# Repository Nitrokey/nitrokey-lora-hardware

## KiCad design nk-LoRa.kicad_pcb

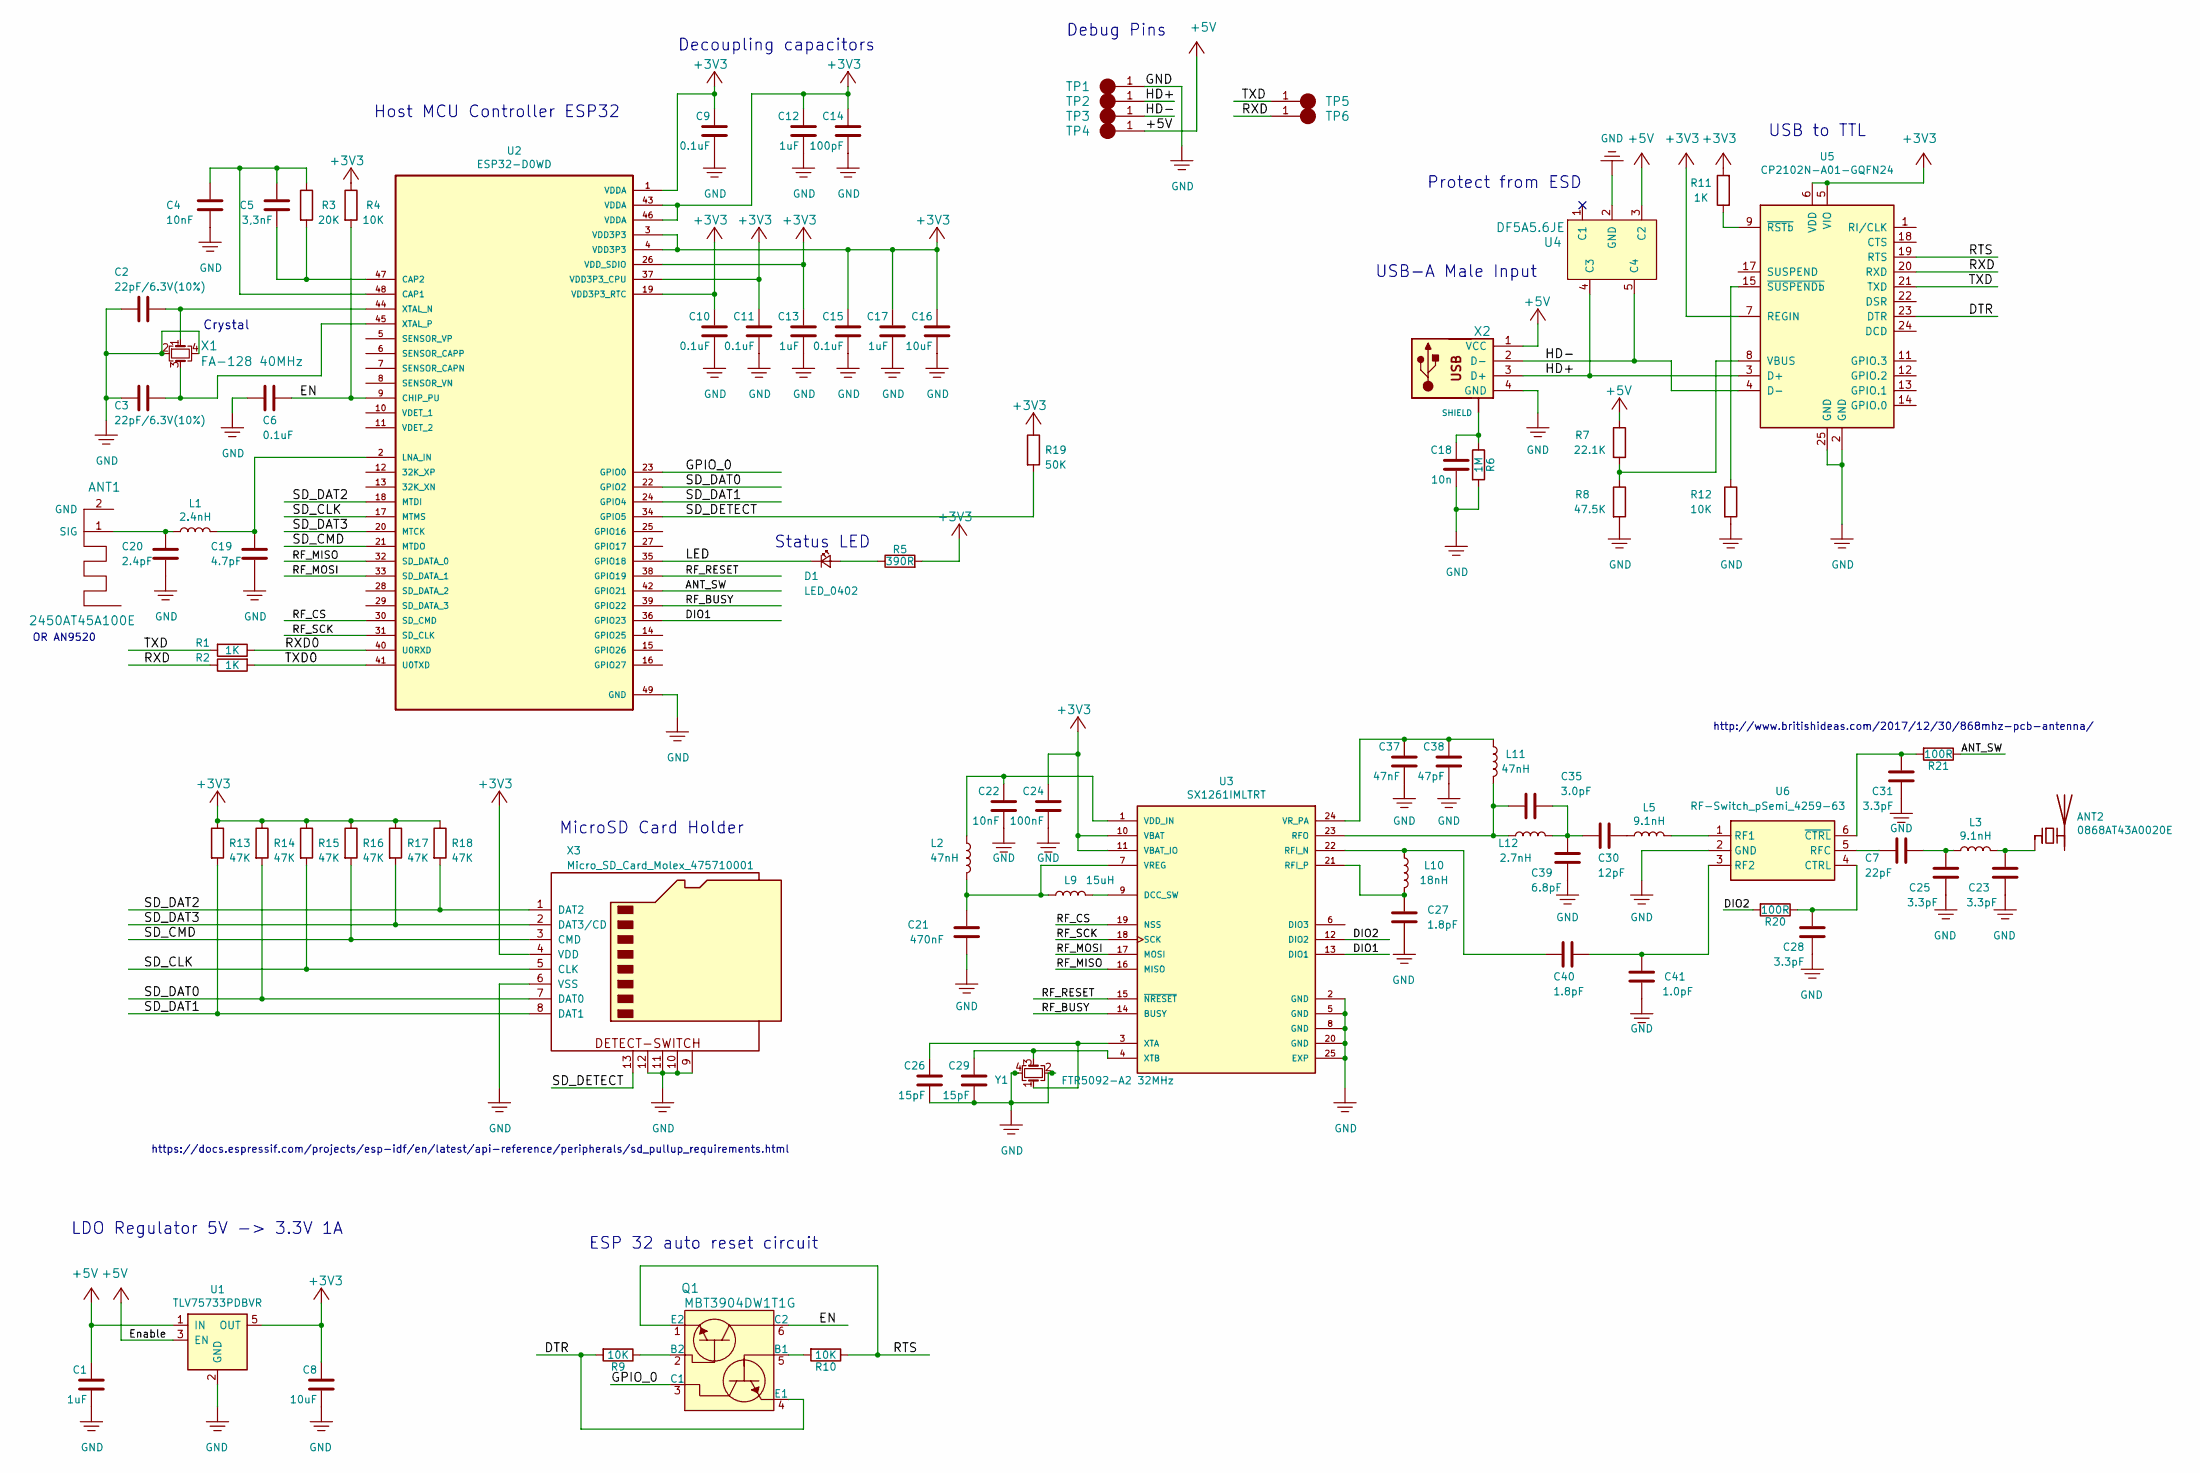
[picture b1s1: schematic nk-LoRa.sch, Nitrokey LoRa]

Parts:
ANT1: 2450AT45A100E; 9520_WiFiChipAntenna
ANT2: 0868AT43A0020E; Ant_868MHz_0868AT43A0020E
C1, C12, C13, C17: 1uF; C_0402_1005Metric; MFG Part Num ?
C2, C3: 22pF/6.3V(10%); C_0402_1005Metric; MFG Part Num ?
C4, C22: 10nF; C_0402_1005Metric; MFG Part Num ?
C5: 3,3nF; C_0402_1005Metric; MFG Part Num ?
C6, C9, C10, C11, C15: 0.1uF; C_0402_1005Metric; MFG Part Num ?
C7: 22pF; C_0402_1005Metric
C8, C16: 10uF; C_0603_1608Metric; MFG Part Num ?
C14: 100pF; C_0402_1005Metric; MFG Part Num ?
C18: 10n; C_0402_1005Metric; MFG Part Num ?
C19: 4.7pF; C_0402_1005Metric
C20: 2.4pF; C_0402_1005Metric
C21: 470nF; C_0402_1005Metric; MFG Part Num GRM155R61A474KE15D
C23, C25, C28, C31: 3.3pF; C_0402_1005Metric
C24: 100nF; C_0402_1005Metric; MFG Part Num GRM155R71C104KA88D
C26, C29: 15pF; C_0402_1005Metric; MFG Part Num GRM1555C1H150JA01D
C27, C40: 1.8pF; C_0402_1005Metric; MFG Part Num GRM1555C1H1R8BA01D
C30: 12pF; C_0402_1005Metric
C35: 3.0pF; C_0402_1005Metric; MFG Part Num GRM1555C1H3R0BA01D
C37: 47nF; C_0402_1005Metric; MFG Part Num ?
C38: 47pF; C_0402_1005Metric; MFG Part Num ?
C39: 6.8pF; C_0402_1005Metric; MFG Part Num GRM1555C1H6R8BA01D
C41: 1.0pF; C_0402_1005Metric
D1: LED_0402; LED_0402_1005Metric
L1: 2.4nH; L_0402_1005Metric; Part.Nr LQP15MN2N4B02D
L2, L11: 47nH; L_0402_1005Metric; Part.Nr LQW15AN47NJ00D
L3, L5: 9.1nH; L_0402_1005Metric; Part.Nr LQW15AN9N1H00D
L9: 15uH; L_0805_2012Metric; Part.Nr MLZ2012M150W
L10: 18nH; L_0402_1005Metric; Part.Nr LQW15AN18NH00D
L12: 2.7nH; L_0402_1005Metric; Part.Nr LQW15AN2N7C00D
Q1: MBT3904DW1T1G; SOT-363_SC-70-6; MPN MBT3904DW1T1G; Digi-Key_PN MBT3904DW1T1GOSCT-ND
R1, R2, R11: 1K; R_0402_1005Metric; MFG Part Num ?
R3: 20K; R_0402_1005Metric; MFG Part Num ?
R4, R9, R10, R12: 10K; R_0402_1005Metric; MFG Part Num ?
R5: 390R; R_0402_1005Metric; MFG Part Num ?
R6: 1M; R_0402_1005Metric; MFG Part Num ?
R7: 22.1K; R_0402_1005Metric; MFG Part Num ?
R8: 47.5K; R_0402_1005Metric; MFG Part Num ?
R13, R14, R15, R16, R17, R18: 47K; R_0402_1005Metric; MFG Part Num ?
R19: 50K; R_0402_1005Metric; MFG Part Num ?
R20, R21: 100R; R_0402_1005Metric; MFG Part Num ?
TP1, TP2, TP3, TP4, TP5, TP6: debug-pin; Prog_Pad_Circular
U1: TLV75733PDBVR; SOT-23-5
U2: ESP32-D0WD; QFN-48-1EP_5x5mm_P0.35mm_EP3.7x3.7mm_ThermalVias
U3: SX1261IMLTRT; QFN-24-1EP_4x4mm_P0.5mm_EP2.7x2.7mm_ThermalVias
U4: DF5A5.6JE; SOT-553; MFG Part Num DF5A5.6JE,LM
U5: CP2102N-A01-GQFN24; QFN-24-1EP_4x4mm_P0.5mm_EP2.6x2.6mm
U6: RF-Switch_pSemi_4259-63; SC-70-6
X1: FA-128 40MHz; Crystal_SMD_2016-4Pin_2.0x1.6mm
X2: USB_Plug; USB-A-PLUG
X3: Micro_SD_Card_Molex_475710001; 47571-0001
Y1: FTR5092-A2 32MHz; Crystal_SMD_2016-4Pin_2.0x1.6mm

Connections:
+3V3: C8.1, C9.1, C10.1, C11.1, C12.1, C13.1, C14.1, C15.1, C16.1, C17.1, C24.1, R4.1, R5.2, R11.2, R13.1, R14.1, R15.1, R16.1, R17.1, R18.1, R19.1, U1.5 (OUT), U2.1 (VDDA), U2.3 (VDD3P3), U2.4 (VDD3P3), U2.19 (VDD3P3_RTC), U2.26 (VDD_SDIO), U2.37 (VDD3P3_CPU), U2.43 (VDDA), U2.46 (VDDA), U3.10 (VBAT), U3.11 (VBAT_IO), U5.5 (VIO), U5.6 (VDD), U5.7 (REGIN), X3.4 (VDD)
+5V: C1.1, R7.1, TP4.1, U1.1 (IN), U1.3 (EN), U4.3 (C2), X2.1 (VCC)
/ANT_SW: R21.1, U2.42 (GPIO21)
/DIO1: U2.36 (GPIO23), U3.13 (DIO1)
/DIO2: R20.2, U3.12 (DIO2)
/DTR: Q1.4 (E1), R9.2, U5.23 (DTR)
/EN: C6.1, Q1.6 (C2), R4.2, U2.9 (CHIP_PU)
/GPIO_0: Q1.3 (C1), U2.23 (GPIO0)
/HD+: TP2.1, U4.4 (C3), U5.3 (D+), X2.3 (D+)
/HD-: TP3.1, U4.5 (C4), U5.4 (D-), X2.2 (D-)
/LED: D1.1 (K), U2.35 (GPIO18)
/RF_BUSY: U2.39 (GPIO22), U3.14 (BUSY)
/RF_CS: U2.30 (SD_CMD), U3.19 (NSS)
/RF_MISO: U2.32 (SD_DATA_0), U3.16 (MISO)
/RF_MOSI: U2.33 (SD_DATA_1), U3.17 (MOSI)
/RF_RESET: U2.38 (GPIO19), U3.15 (~NRESET~)
/RF_SCK: U2.31 (SD_CLK), U3.18 (SCK)
/RTS: Q1.1 (E2), R10.1, U5.19 (RTS)
/RXD: R2.1, TP6.1, U5.20 (RXD)
/RXD0: R1.1, U2.40 (U0RXD)
/SD_CLK: R15.2, U2.17 (MTMS), X3.5 (CLK)
/SD_CMD: R16.2, U2.21 (MTDO), X3.3 (CMD)
/SD_DAT0: R14.2, U2.22 (GPIO2), X3.7 (DAT0)
/SD_DAT1: R13.2, U2.24 (GPIO4), X3.8 (DAT1)
/SD_DAT2: R18.2, U2.18 (MTDI), X3.1 (DAT2)
/SD_DAT3: R17.2, U2.20 (MTCK), X3.2 (DAT3/CD)
/SD_DETECT: R19.2, U2.34 (GPIO5), X3.13 (GND)
/TXD: R1.2, TP5.1, U5.21 (TXD)
/TXD0: R2.2, U2.41 (U0TXD)
GND: C1.2, C2.2, C3.2, C4.1, C6.2, C8.2, C9.2, C10.2, C11.2, C12.2, C13.2, C14.2, C15.2, C16.2, C17.2, C18.2, C19.2, C20.2, C21.2, C22.2, C23.2, C24.2, C25.2, C26.2, C27.1, C28.2, C29.2, C31.2, C37.2, C38.2, C39.1, C41.2, R6.2, R8.2, R12.2, TP1.1, U1.2 (GND), U2.49 (GND), U3.2 (GND), U3.5 (GND), U3.8 (GND), U3.20 (GND), U3.25 (EXP), U4.2 (GND), U5.2 (GND), U5.25 (GND), U6.2 (GND), X1.2, X1.4, X2.4 (GND), X3.6 (VSS), X3.9 (SW1), X3.10 (SW2), X3.11 (GND), X3.12 (GND), Y1.2, Y1.4
unnamed: ANT1.1 (SIG), C20.1, L1.1
unnamed: ANT2.1 (FEED), C23.1, L3.1
unnamed: C2.1, U2.44 (XTAL_N), X1.1
unnamed: C3.1, U2.45 (XTAL_P), X1.3
unnamed: C4.2, C5.1, R3.1, U2.48 (CAP1)
unnamed: C5.2, R3.2, U2.47 (CAP2)
unnamed: C7.2, U6.5 (RFC)
unnamed: C18.1, R6.1, X2.5 (NC1), X2.6 (SHIELD)
unnamed: C19.1, L1.2, U2.2 (LNA_IN)
unnamed: C21.1, L2.1, L9.2, U3.7 (VREG)
unnamed: C22.1, L2.2, U3.1 (VDD_IN)
unnamed: C7.1, C25.1, L3.2
unnamed: C26.1, U3.3 (XTA), Y1.1
unnamed: C27.2, L10.2, U3.21 (RFI_P)
unnamed: C28.1, R20.1, U6.4 (CTRL)
unnamed: C29.1, U3.4 (XTB), Y1.3
unnamed: C30.1, L5.2
unnamed: C30.2, C35.1, C39.2, L12.2
unnamed: C31.1, R21.2, U6.6 (~CTRL)
unnamed: C35.2, L11.1, L12.1, U3.23 (RFO)
unnamed: C37.1, C38.1, L11.2, U3.24 (VR_PA)
unnamed: C40.1, C41.1, U6.3 (RF2)
unnamed: C40.2, L10.1, U3.22 (RFI_N)
unnamed: D1.2 (A), R5.1
unnamed: L5.1, U6.1 (RF1)
unnamed: L9.1, U3.9 (DCC_SW)
unnamed: Q1.2 (B2), R9.1
unnamed: Q1.5 (B1), R10.2
unnamed: R7.2, R8.1, U5.8 (VBUS)
unnamed: R11.1, U5.9 (~RSTb)
unnamed: R12.1, U5.15 (~SUSPENDb)

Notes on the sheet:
Protect from ESD
USB-A Male Input
Host MCU Controller ESP32
Status LED
Decoupling capacitors
Debug Pins
ESP 32 auto reset circuit
USB to TTL
MicroSD Card Holder
Crystal
http://www.britishideas.com/2017/12/30/868mhz-pcb-antenna/
https://docs.espressif.com/projects/esp-idf/en/latest/api-reference/peripherals/sd_pullup_requirements.html
OR AN9520
LDO Regulator 5V -> 3.3V 1A

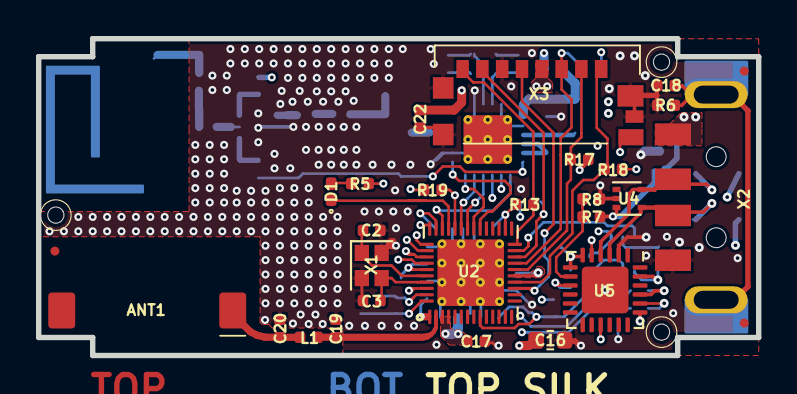
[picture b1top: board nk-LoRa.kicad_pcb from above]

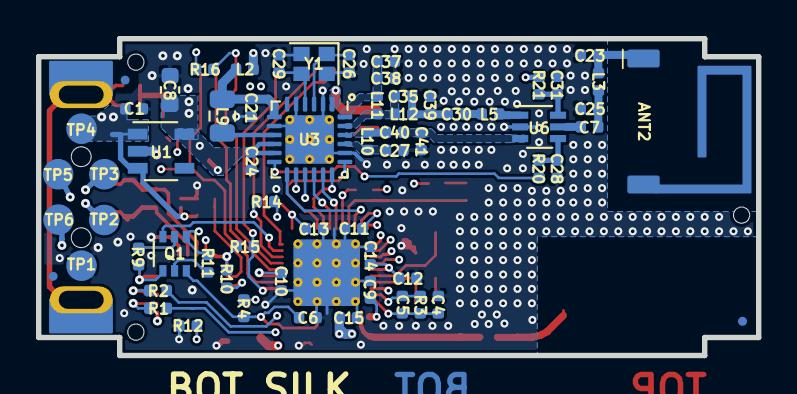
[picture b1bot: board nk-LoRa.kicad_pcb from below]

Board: 4 copper layers, 40.0 x 17.6 mm, 93 parts (65 on the bottom side), 61 nets.

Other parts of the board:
3D_*: case_bottom
FID3, FID3#2, FID3#3, FID3#4, FID3#5, FID3#6: Fiducial_0.5mm_Dia_1mm_Outer

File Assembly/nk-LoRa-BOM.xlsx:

BOM - NITROKEY LoRa Rev.1
Reference | Quantity | Value | Footprint | Manufacturer Part Number | Distributer Link
ANT1 | 1 | 2450 MHZ ANTENNA | footprints:9520_WiFiChipAntenna | 2450AT45A100E | https://www.mouser.de/ProductDetail/Johanson-Technology/2450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
ANT2 | 1 | 868 MHZ ANTENNA | footprints:Ant_868MHz_0868AT43A0020E | 0868AT43A0020E | https://www.digikey.com/product-detail/en/johanson-technolog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
C14 | 1 | 100pF | Capacitor_SMD:C_0402_1005Metric | GRM1555C1H101FA01J | https://www.mouser.de/ProductDetail/Murata-Electronics/GRM15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
C16 C8 | 2 | 10uF | Capacitor_SMD:C_0603_1608Metric | GRM188R61A106KE69J | https://www.mouser.de/ProductDetail/Murata-Electronics/GRM18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
C1 C12 C13 C17 | 4 | 1uF | Capacitor_SMD:C_0402_1005Metric | GRM155C81A105KA12D | https://www.mouser.de/ProductDetail/Murata-Electronics/GRM15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
C18 | 1 | 10n | Capacitor_SMD:C_0402_1005Metric | GRM155R71E103KA01D | https://www.mouser.de/ProductDetail/Murata-Electronics/GRM15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
C19 | 1 | 4.7pF | Capacitor_SMD:C_0402_1005Metric | GJM1555C1H2R4CB01D | https://www.mouser.de/ProductDetail/Murata-Electronics/GJM15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
C2 C3 | 2 | 22pF/6.3V(10%) | Capacitor_SMD:C_0402_1005Metric | GRM1555C1H220FA01D | https://www.mouser.de/ProductDetail/Murata-Electronics/GRM15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
C20 | 1 | 2.4pF | Capacitor_SMD:C_0402_1005Metric | GJM1555C1H2R4CB01J | https://www.mouser.de/ProductDetail/Murata-Electronics/GJM15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
C21 | 1 | 470nF | Capacitor_SMD:C_0402_1005Metric | GRM155R61A474KE15D | https://www.mouser.de/ProductDetail/Murata-Electronics/GRM15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
C23 C25 C28 C31 | 4 | 3.3pF | Capacitor_SMD:C_0402_1005Metric | GRM1555C1H3R3BA01D | https://www.mouser.de/ProductDetail/Murata-Electronics/GRM15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
C27 C40 | 2 | 1.8pF | Capacitor_SMD:C_0402_1005Metric | GRM1555C1H1R8BA01D | https://www.mouser.de/_/?Keyword=GRM1555C1H1R8BA01D
C26 C29 | 2 | 15pF | Capacitor_SMD:C_0402_1005Metric | GRM1555C1H150JA01D | https://www.mouser.de/ProductDetail/Murata-Electronics/GRM15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
C30 | 1 | 12pF | Capacitor_SMD:C_0402_1005Metric | GRM1555C1H120JA01J | https://www.mouser.de/ProductDetail/Murata-Electronics/GRM15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
C35 | 1 | 3.0pF | Capacitor_SMD:C_0402_1005Metric | GRM1555C1H3R0BA01D | https://www.mouser.de/ProductDetail/Murata-Electronics/GRM15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
C37 | 1 | 47nF | Capacitor_SMD:C_0402_1005Metric | GRM155R71C473KA01J | https://www.mouser.de/ProductDetail/Murata-Electronics/GRM15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
C38 | 1 | 47pF | Capacitor_SMD:C_0402_1005Metric | GJM1555C1H470FB01D | https://www.mouser.de/ProductDetail/Murata-Electronics/GJM15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
C39 | 1 | 6.8pF | Capacitor_SMD:C_0402_1005Metric | GRM1555C1H6R8BA01D | https://www.mouser.de/ProductDetail/Murata-Electronics/GRM15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
C22 C4 | 2 | 10nF | Capacitor_SMD:C_0402_1005Metric | GRM155R71E103KA01D | https://www.mouser.de/ProductDetail/Murata-Electronics/GRM15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
C41 | 1 | 1.0pF | Capacitor_SMD:C_0402_1005Metric | GRM1555C1H1R0BA01D | https://www.mouser.de/ProductDetail/Murata-Electronics/GRM15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
C5 | 1 | 3,3nF | Capacitor_SMD:C_0402_1005Metric | GRM155R71H332JA01D | https://www.mouser.de/ProductDetail/Murata-Electronics/GRM15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
C7 | 1 | 22pF | Capacitor_SMD:C_0402_1005Metric | GRM1555C1H220JA01D | https://www.mouser.de/ProductDetail/Murata-Electronics/GRM15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
C10 C11 C15 C24 C6 C9 | 6 | 0.1uF | Capacitor_SMD:C_0402_1005Metric | GRM155R71C104KA88D | https://www.mouser.de/ProductDetail/Murata-Electronics/GRM15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
D1 | 1 | LED_0402 | LED_SMD:LED_0402_1005Metric | APHHS1005SURCK | https://www.mouser.de/ProductDetail/Kingbright/APHHS1005SURC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
L1 | 1 | 2.4nH | Inductor_SMD:L_0402_1005Metric | LQP15MN2N4B02D | https://www.mouser.de/ProductDetail/Murata-Electronics/LQP15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
L10 | 1 | 18nH | Inductor_SMD:L_0402_1005Metric | LQW15AN18NH00D | https://www.mouser.de/ProductDetail/Murata-Electronics/LQW15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
L12 | 1 | 2.7nH | Inductor_SMD:L_0402_1005Metric | LQW15AN2N7C00D | https://www.mouser.de/ProductDetail/Murata-Electronics/LQW15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
L11 L2 | 2 | 47nH | Inductor_SMD:L_0402_1005Metric | LQW15AN47NJ00D | https://www.mouser.de/ProductDetail/Murata-Electronics/LQW15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
L3 L5 | 2 | 9.1nH | Inductor_SMD:L_0402_1005Metric | LQW15AN9N1H00D | https://www.mouser.de/ProductDetail/Murata-Electronics/LQW15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
L9 | 1 | 15uH | Inductor_SMD:L_0805_2012Metric | MLZ2012M150W | https://www.mouser.de/ProductDetail/TDK/MLZ2012M150WTD25?qs=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
Q1 | 1 | MBT3904DW1T1G | Package_TO_SOT_SMD:SOT-363_SC-70-6 | http://www.onsemi.com/pub/Collateral/MBT3904DW1T1-D.PDF | https://www.mouser.de/ProductDetail/ON-Semiconductor/MBT3904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
R10 R12 R4 R9 | 4 | 10K | Resistor_SMD:R_0402_1005Metric | http://www.vishay.com/docs/20035/dcrcwe3.pdf | https://www.mouser.de/ProductDetail/Vishay-Dale/CRCW040210K0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
R13 R14 R15 R16 R17 R18 | 6 | 47K | Resistor_SMD:R_0402_1005Metric | http://www.vishay.com/docs/20035/dcrcwe3.pdf | Vishay Standard
R19 | 1 | 50K | Resistor_SMD:R_0402_1005Metric | http://www.vishay.com/docs/20035/dcrcwe3.pdf | Vishay Standard
R1 R11 R2 | 3 | 1K | Resistor_SMD:R_0402_1005Metric | http://www.vishay.com/docs/20035/dcrcwe3.pdf | Vishay Standard
R20 R21 | 2 | 100R | Resistor_SMD:R_0402_1005Metric | http://www.vishay.com/docs/20035/dcrcwe3.pdf | Vishay Standard
R3 | 1 | 20K | Resistor_SMD:R_0402_1005Metric | http://www.vishay.com/docs/20035/dcrcwe3.pdf | Vishay Standard
R5 | 1 | 390R | Resistor_SMD:R_0402_1005Metric | http://www.vishay.com/docs/20035/dcrcwe3.pdf | Vishay Standard
R6 | 1 | 1M | Resistor_SMD:R_0402_1005Metric | http://www.vishay.com/docs/20035/dcrcwe3.pdf | Vishay Standard
R7 | 1 | 22.1K | Resistor_SMD:R_0402_1005Metric | http://www.vishay.com/docs/20035/dcrcwe3.pdf | Vishay Standard
R8 | 1 | 47.5K | Resistor_SMD:R_0402_1005Metric | http://www.vishay.com/docs/20035/dcrcwe3.pdf | Vishay Standard
U1 | 1 | TLV75733PDBVR | footprints:SOT-23-5 | TLV75733PDBVR | https://www.mouser.de/ProductDetail/Texas-Instruments/TLV757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
U2 | 1 | ESP32-D0WD | Package_DFN_QFN:QFN-48-1EP_5x5mm_P0.35mm_EP3.7x3.7mm_ThermalVias | Smd Ic Esp32-D0wd, Dual Core Mcu, Espressif Systems | https://www.mouser.de/ProductDetail/Espressif-Systems/ESP32-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
U3 | 1 | SX1261IMLTRT | footprints:QFN-24-1EP_4x4mm_P0.5mm_EP2.7x2.7mm_ThermalVias | RF Transceiver FSK 1.8V to 3.7V 150MHz to 960MHz 24-Pin QFN | https://www.mouser.de/ProductDetail/Semtech/SX1261IMLTRT?qs=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
U4 | 1 | DF5A5.6JE | Package_TO_SOT_SMD:SOT-553 | http://optoelectronics.liteon.com/upload/download/DS22-2008-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 | https://www.mouser.de/ProductDetail/Toshiba/DF5A56JELM?qs=%2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
U5 | 1 | CP2102N-A01-GQFN24 | Package_DFN_QFN:QFN-24-1EP_4x4mm_P0.5mm_EP2.6x2.6mm | CP2102N-A01-GQFN24 | https://www.mouser.de/ProductDetail/Silicon-Labs/CP2102N-A01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
U6 | 1 | RF-Switch_pSemi_4259-63 | footprints:SC-70-6 | RF-Switch_pSemi_4259-63 | https://www.digikey.com/product-detail/en/psemi/4259-63/1046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
X1 | 1 | FA-128 40MHz | Crystal:Crystal_SMD_2016-4Pin_2.0x1.6mm | FA-128 40MHz | https://www.digikey.com/product-detail/en/epson/FA-128-40.00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
X2 | 1 | USB_Plug | footprints:USB-A-PLUG | USB_Plug | 0480372200_sd
X3 | 1 | Micro_SD_Card_Molex_475710001 | footprints:47571-0001 | Micro_SD_Card_Molex_475710001 | https://www.digikey.de/product-detail/de/molex/0475710001/WM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
Y1 | 1 | Q 32,0-JXS21-10-10/10-FU-WA-LF | Crystal:Crystal_SMD_2016-4Pin_2.0x1.6mm | Q 32,0-JXS21-10-10/10-FU-WA-LF | https://www.digikey.com/product-detail/en/jauch-quartz/Q-320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

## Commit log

2019-07-25 Silk screen labels for C35 and L12 fixed
